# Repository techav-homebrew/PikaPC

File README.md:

# PikaPC

A PowerPC 403GA Homebrew Computer

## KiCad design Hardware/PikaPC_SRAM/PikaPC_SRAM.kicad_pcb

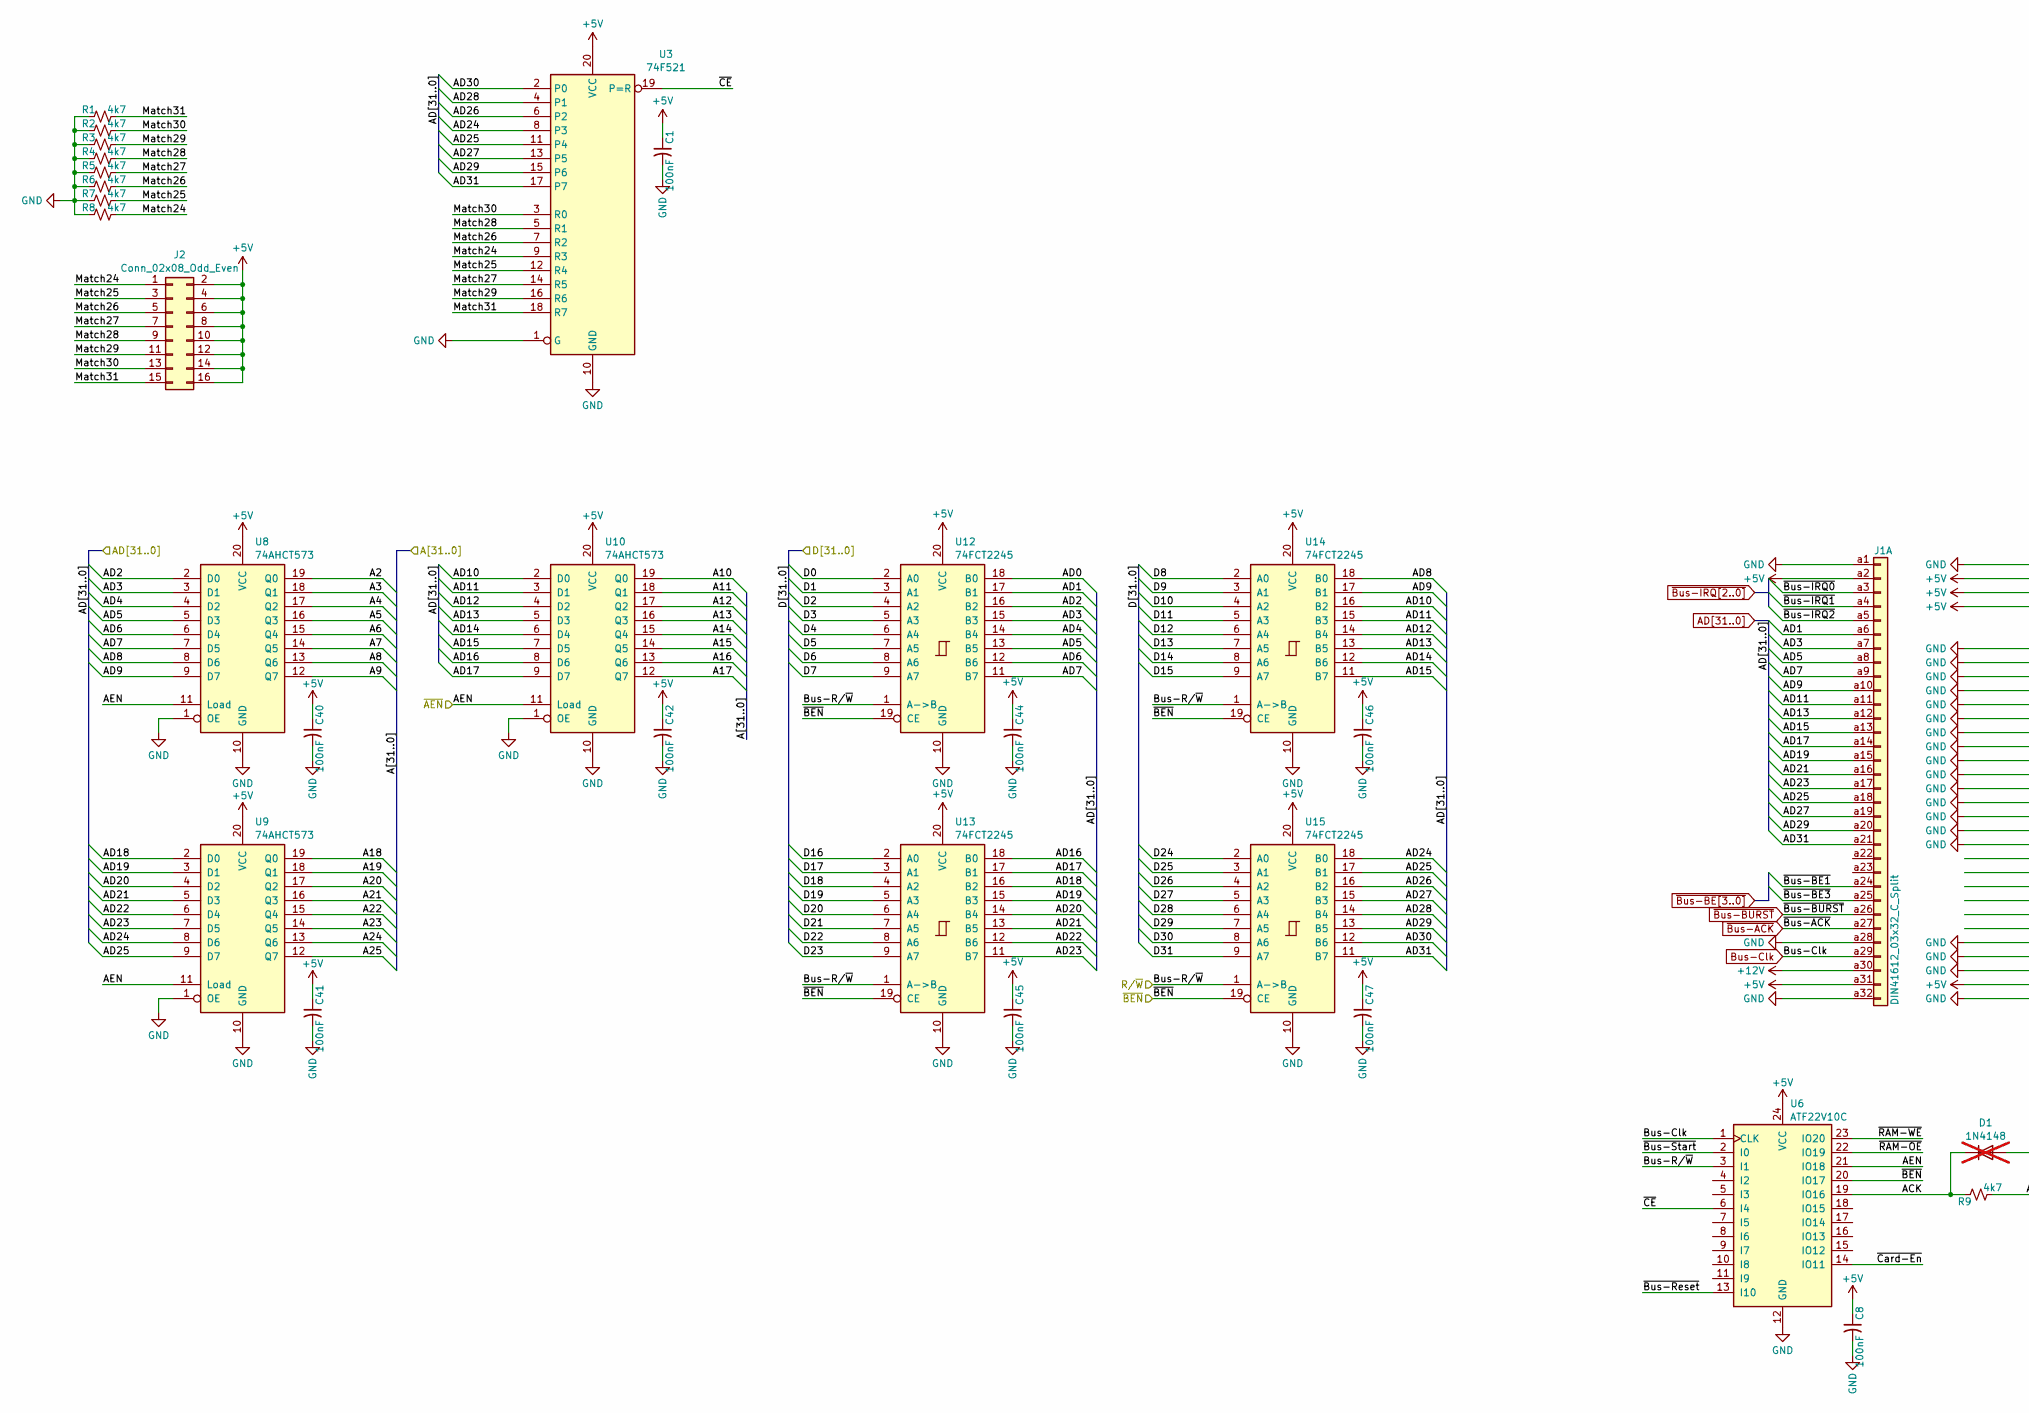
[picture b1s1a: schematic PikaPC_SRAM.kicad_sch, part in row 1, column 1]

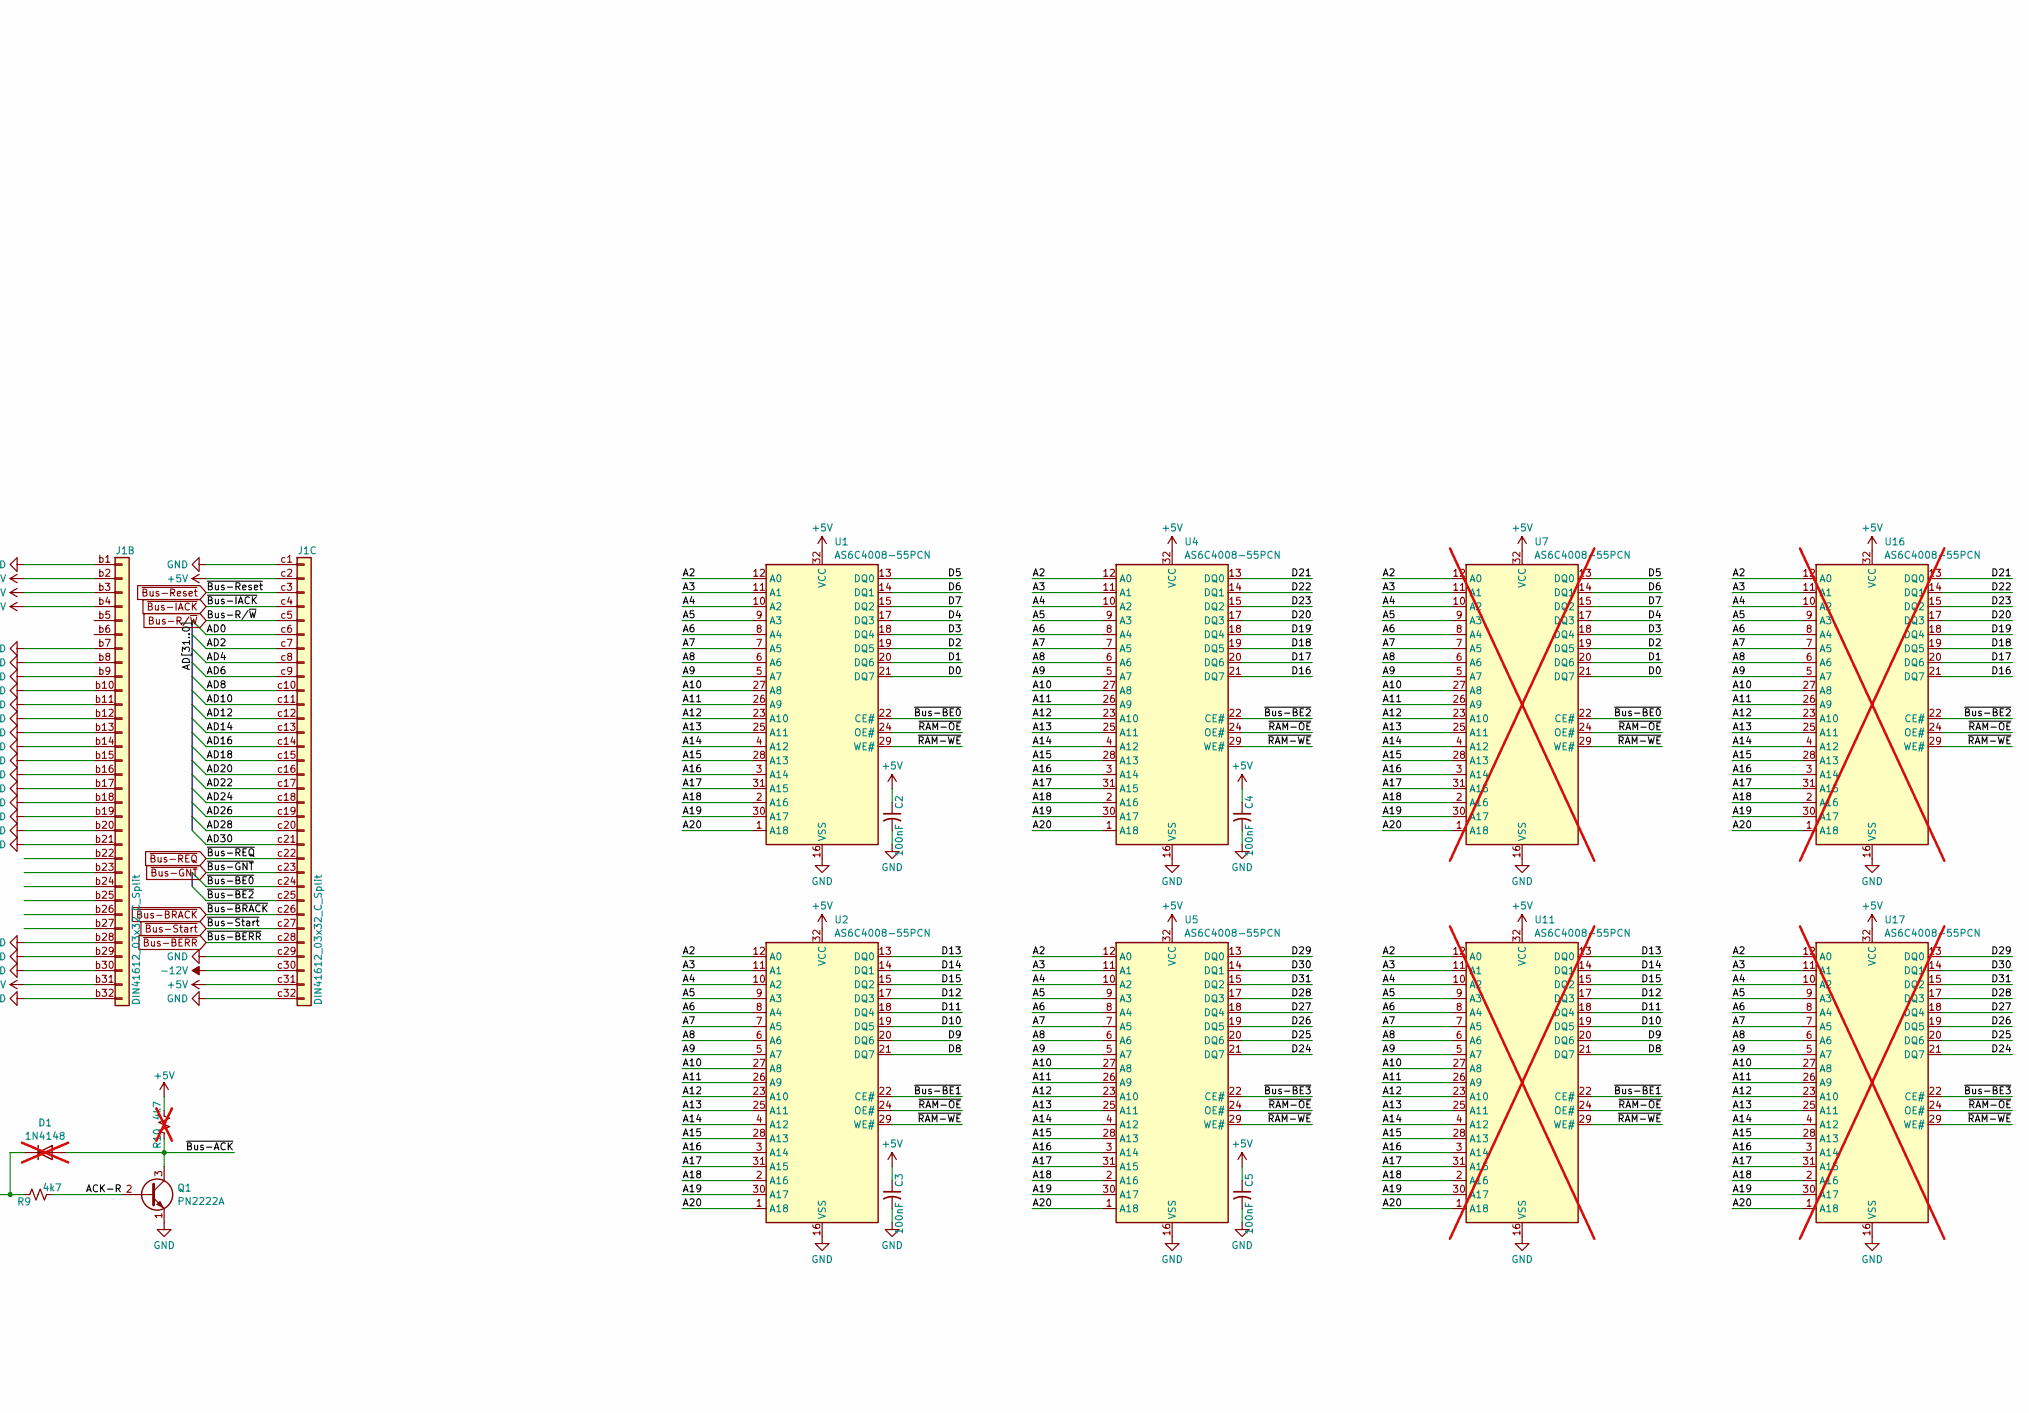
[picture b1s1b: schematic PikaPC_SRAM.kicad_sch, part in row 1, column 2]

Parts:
C1, C2, C3, C4, C5, C8, C40, C41, C42, C44, C45, C46, C47: 100nF; C_0805_2012Metric; Mouser 187-CL21B104KACNNNC
D1: 1N4148; D_DO-35_SOD27_P7.62mm_Horizontal; not fitted
J1: DIN41612_03x32_C_Split; DIN41612_C_3x32_Male_Horizontal_THT
J2: Conn_02x08_Odd_Even; PinHeader_2x08_P2.54mm_Vertical
Q1: PN2222A; TO-92_Inline
R1, R2, R3, R4, R5, R6, R7, R8, R9: 4k7; R_0805_2012Metric; Mouser 303-0805W8J0472T5E
R10: 4k7; R_0805_2012Metric; Mouser 303-0805W8J0472T5E; not fitted
U1, U2, U4, U5: AS6C4008-55PCN; DIP-32_W15.24mm
U3: 74F521; SOIC-20W_7.5x12.8mm_P1.27mm; Mouser 595-SN74F521DWR
U6: ATF22V10C; DIP-24_W7.62mm_Socket; Mouser 556-ATF22V10C-10PU
U7, U11, U16, U17: AS6C4008-55PCN; SOP-32_11.305x20.495mm_P1.27mm; not fitted
U8, U9, U10: 74AHCT573; TSSOP-20_4.4x6.5mm_P0.65mm; Mouser 771-74AHCT573PW-T
U12, U13, U14, U15: 74FCT2245; SOIC-20W_7.5x12.8mm_P1.27mm; Mouser 595-CY74FCT2245TSOCT

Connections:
+5V: C1.1, C2.1, C3.1, C4.1, C5.1, C8.1, C40.1, C41.1, C42.1, C44.1, C45.1, C46.1, C47.1, J1.a2, J1.a31, J1.b2, J1.b3, J1.b4, J1.b31, J1.c2, J1.c31, J2.2, J2.4, J2.6, J2.8, J2.10, J2.12, J2.14, J2.16, R10.2, U1.32 (VCC), U2.32 (VCC), U3.20 (VCC), U4.32 (VCC), U5.32 (VCC), U6.24 (VCC), U7.32 (VCC), U8.20 (VCC), U9.20 (VCC), U10.20 (VCC), U11.32 (VCC), U12.20 (VCC), U13.20 (VCC), U14.20 (VCC), U15.20 (VCC), U16.32 (VCC), U17.32 (VCC)
+12V: J1.a30
-12V: J1.c30
/A2: U1.12 (A0), U2.12 (A0), U4.12 (A0), U5.12 (A0), U7.12 (A0), U8.19 (Q0), U11.12 (A0), U16.12 (A0), U17.12 (A0)
/A3: U1.11 (A1), U2.11 (A1), U4.11 (A1), U5.11 (A1), U7.11 (A1), U8.18 (Q1), U11.11 (A1), U16.11 (A1), U17.11 (A1)
/A4: U1.10 (A2), U2.10 (A2), U4.10 (A2), U5.10 (A2), U7.10 (A2), U8.17 (Q2), U11.10 (A2), U16.10 (A2), U17.10 (A2)
/A5: U1.9 (A3), U2.9 (A3), U4.9 (A3), U5.9 (A3), U7.9 (A3), U8.16 (Q3), U11.9 (A3), U16.9 (A3), U17.9 (A3)
/A6: U1.8 (A4), U2.8 (A4), U4.8 (A4), U5.8 (A4), U7.8 (A4), U8.15 (Q4), U11.8 (A4), U16.8 (A4), U17.8 (A4)
/A7: U1.7 (A5), U2.7 (A5), U4.7 (A5), U5.7 (A5), U7.7 (A5), U8.14 (Q5), U11.7 (A5), U16.7 (A5), U17.7 (A5)
/A8: U1.6 (A6), U2.6 (A6), U4.6 (A6), U5.6 (A6), U7.6 (A6), U8.13 (Q6), U11.6 (A6), U16.6 (A6), U17.6 (A6)
/A9: U1.5 (A7), U2.5 (A7), U4.5 (A7), U5.5 (A7), U7.5 (A7), U8.12 (Q7), U11.5 (A7), U16.5 (A7), U17.5 (A7)
/A10: U1.27 (A8), U2.27 (A8), U4.27 (A8), U5.27 (A8), U7.27 (A8), U10.19 (Q0), U11.27 (A8), U16.27 (A8), U17.27 (A8)
/A11: U1.26 (A9), U2.26 (A9), U4.26 (A9), U5.26 (A9), U7.26 (A9), U10.18 (Q1), U11.26 (A9), U16.26 (A9), U17.26 (A9)
/A12: U1.23 (A10), U2.23 (A10), U4.23 (A10), U5.23 (A10), U7.23 (A10), U10.17 (Q2), U11.23 (A10), U16.23 (A10), U17.23 (A10)
/A13: U1.25 (A11), U2.25 (A11), U4.25 (A11), U5.25 (A11), U7.25 (A11), U10.16 (Q3), U11.25 (A11), U16.25 (A11), U17.25 (A11)
/A14: U1.4 (A12), U2.4 (A12), U4.4 (A12), U5.4 (A12), U7.4 (A12), U10.15 (Q4), U11.4 (A12), U16.4 (A12), U17.4 (A12)
/A15: U1.28 (A13), U2.28 (A13), U4.28 (A13), U5.28 (A13), U7.28 (A13), U10.14 (Q5), U11.28 (A13), U16.28 (A13), U17.28 (A13)
/A16: U1.3 (A14), U2.3 (A14), U4.3 (A14), U5.3 (A14), U7.3 (A14), U10.13 (Q6), U11.3 (A14), U16.3 (A14), U17.3 (A14)
/A17: U1.31 (A15), U2.31 (A15), U4.31 (A15), U5.31 (A15), U7.31 (A15), U10.12 (Q7), U11.31 (A15), U16.31 (A15), U17.31 (A15)
/A18: U1.2 (A16), U2.2 (A16), U4.2 (A16), U5.2 (A16), U7.2 (A16), U9.19 (Q0), U11.2 (A16), U16.2 (A16), U17.2 (A16)
/A19: U1.30 (A17), U2.30 (A17), U4.30 (A17), U5.30 (A17), U7.30 (A17), U9.18 (Q1), U11.30 (A17), U16.30 (A17), U17.30 (A17)
/A20: U1.1 (A18), U2.1 (A18), U4.1 (A18), U5.1 (A18), U7.1 (A18), U9.17 (Q2), U11.1 (A18), U16.1 (A18), U17.1 (A18)
/A21: U9.16 (Q3)
/A22: U9.15 (Q4)
/A23: U9.14 (Q5)
/A24: U9.13 (Q6)
/A25: U9.12 (Q7)
/ACK: D1.1 (K), R9.1, U6.19 (IO16)
/ACK-R: Q1.2 (B), R9.2
/AEN: U6.21 (IO18), U8.11 (Load), U9.11 (Load), U10.11 (Load)
/D0: U1.21 (DQ7), U7.21 (DQ7), U12.2 (A0)
/D1: U1.20 (DQ6), U7.20 (DQ6), U12.3 (A1)
/D2: U1.19 (DQ5), U7.19 (DQ5), U12.4 (A2)
/D3: U1.18 (DQ4), U7.18 (DQ4), U12.5 (A3)
/D4: U1.17 (DQ3), U7.17 (DQ3), U12.6 (A4)
/D5: U1.13 (DQ0), U7.13 (DQ0), U12.7 (A5)
/D6: U1.14 (DQ1), U7.14 (DQ1), U12.8 (A6)
/D7: U1.15 (DQ2), U7.15 (DQ2), U12.9 (A7)
/D8: U2.21 (DQ7), U11.21 (DQ7), U14.2 (A0)
/D9: U2.20 (DQ6), U11.20 (DQ6), U14.3 (A1)
/D10: U2.19 (DQ5), U11.19 (DQ5), U14.4 (A2)
/D11: U2.18 (DQ4), U11.18 (DQ4), U14.5 (A3)
/D12: U2.17 (DQ3), U11.17 (DQ3), U14.6 (A4)
/D13: U2.13 (DQ0), U11.13 (DQ0), U14.7 (A5)
/D14: U2.14 (DQ1), U11.14 (DQ1), U14.8 (A6)
/D15: U2.15 (DQ2), U11.15 (DQ2), U14.9 (A7)
/D16: U4.21 (DQ7), U13.2 (A0), U16.21 (DQ7)
/D17: U4.20 (DQ6), U13.3 (A1), U16.20 (DQ6)
/D18: U4.19 (DQ5), U13.4 (A2), U16.19 (DQ5)
/D19: U4.18 (DQ4), U13.5 (A3), U16.18 (DQ4)
/D20: U4.17 (DQ3), U13.6 (A4), U16.17 (DQ3)
/D21: U4.13 (DQ0), U13.7 (A5), U16.13 (DQ0)
/D22: U4.14 (DQ1), U13.8 (A6), U16.14 (DQ1)
/D23: U4.15 (DQ2), U13.9 (A7), U16.15 (DQ2)
/D24: U5.21 (DQ7), U15.2 (A0), U17.21 (DQ7)
/D25: U5.20 (DQ6), U15.3 (A1), U17.20 (DQ6)
/D26: U5.19 (DQ5), U15.4 (A2), U17.19 (DQ5)
/D27: U5.18 (DQ4), U15.5 (A3), U17.18 (DQ4)
/D28: U5.17 (DQ3), U15.6 (A4), U17.17 (DQ3)
/D29: U5.13 (DQ0), U15.7 (A5), U17.13 (DQ0)
/D30: U5.14 (DQ1), U15.8 (A6), U17.14 (DQ1)
/D31: U5.15 (DQ2), U15.9 (A7), U17.15 (DQ2)
/Match24: J2.1, R8.2, U3.9 (R3)
/Match25: J2.3, R7.2, U3.12 (R4)
/Match26: J2.5, R6.2, U3.7 (R2)
/Match27: J2.7, R5.2, U3.14 (R5)
/Match28: J2.9, R4.2, U3.5 (R1)
/Match29: J2.11, R3.2, U3.16 (R6)
/Match30: J2.13, R2.2, U3.3 (R0)
/Match31: J2.15, R1.2, U3.18 (R7)
/~BEN: U6.20 (IO17), U12.19 (CE), U13.19 (CE), U14.19 (CE), U15.19 (CE)
/~CE: U3.19 (P=R), U6.6 (I4)
/~Card-En: U6.14 (IO11)
/~RAM-OE: U1.24 (OE#), U2.24 (OE#), U4.24 (OE#), U5.24 (OE#), U6.22 (IO19), U7.24 (OE#), U11.24 (OE#), U16.24 (OE#), U17.24 (OE#)
/~RAM-WE: U1.29 (WE#), U2.29 (WE#), U4.29 (WE#), U5.29 (WE#), U6.23 (IO20), U7.29 (WE#), U11.29 (WE#), U16.29 (WE#), U17.29 (WE#)
AD0: J1.c6, U12.18 (B0)
AD1: J1.a6, U12.17 (B1)
AD2: J1.c7, U8.2 (D0), U12.16 (B2)
AD3: J1.a7, U8.3 (D1), U12.15 (B3)
AD4: J1.c8, U8.4 (D2), U12.14 (B4)
AD5: J1.a8, U8.5 (D3), U12.13 (B5)
AD6: J1.c9, U8.6 (D4), U12.12 (B6)
AD7: J1.a9, U8.7 (D5), U12.11 (B7)
AD8: J1.c10, U8.8 (D6), U14.18 (B0)
AD9: J1.a10, U8.9 (D7), U14.17 (B1)
AD10: J1.c11, U10.2 (D0), U14.16 (B2)
AD11: J1.a11, U10.3 (D1), U14.15 (B3)
AD12: J1.c12, U10.4 (D2), U14.14 (B4)
AD13: J1.a12, U10.5 (D3), U14.13 (B5)
AD14: J1.c13, U10.6 (D4), U14.12 (B6)
AD15: J1.a13, U10.7 (D5), U14.11 (B7)
AD16: J1.c14, U10.8 (D6), U13.18 (B0)
AD17: J1.a14, U10.9 (D7), U13.17 (B1)
AD18: J1.c15, U9.2 (D0), U13.16 (B2)
AD19: J1.a15, U9.3 (D1), U13.15 (B3)
AD20: J1.c16, U9.4 (D2), U13.14 (B4)
AD21: J1.a16, U9.5 (D3), U13.13 (B5)
AD22: J1.c17, U9.6 (D4), U13.12 (B6)
AD23: J1.a17, U9.7 (D5), U13.11 (B7)
AD24: J1.c18, U3.8 (P3), U9.8 (D6), U15.18 (B0)
AD25: J1.a18, U3.11 (P4), U9.9 (D7), U15.17 (B1)
AD26: J1.c19, U3.6 (P2), U15.16 (B2)
AD27: J1.a19, U3.13 (P5), U15.15 (B3)
AD28: J1.c20, U3.4 (P1), U15.14 (B4)
AD29: J1.a20, U3.15 (P6), U15.13 (B5)
AD30: J1.c21, U3.2 (P0), U15.12 (B6)
AD31: J1.a21, U3.17 (P7), U15.11 (B7)
Bus-Clk: J1.a29, U6.1 (CLK)
Bus-R/~W: J1.c5, U6.3 (I1), U12.1 (A->B), U13.1 (A->B), U14.1 (A->B), U15.1 (A->B)
GND: C1.2, C2.2, C3.2, C4.2, C5.2, C8.2, C40.2, C41.2, C42.2, C44.2, C45.2, C46.2, C47.2, J1.a1, J1.a28, J1.a32, J1.b1, J1.b7, J1.b8, J1.b9, J1.b10, J1.b11, J1.b12, J1.b13, J1.b14, J1.b15, J1.b16, J1.b17, J1.b18, J1.b19, J1.b20, J1.b21, J1.b28, J1.b29, J1.b30, J1.b32, J1.c1, J1.c29, J1.c32, Q1.1 (E), R1.1, R2.1, R3.1, R4.1, R5.1, R6.1, R7.1, R8.1, U1.16 (VSS), U2.16 (VSS), U3.1 (G), U3.10 (GND), U4.16 (VSS), U5.16 (VSS), U6.12 (GND), U7.16 (VSS), U8.1 (OE), U8.10 (GND), U9.1 (OE), U9.10 (GND), U10.1 (OE), U10.10 (GND), U11.16 (VSS), U12.10 (GND), U13.10 (GND), U14.10 (GND), U15.10 (GND), U16.16 (VSS), U17.16 (VSS)
~Bus-ACK: D1.2 (A), J1.a27, Q1.3 (C), R10.1
~Bus-BE0: J1.c24, U1.22 (CE#), U7.22 (CE#)
~Bus-BE1: J1.a24, U2.22 (CE#), U11.22 (CE#)
~Bus-BE2: J1.c25, U4.22 (CE#), U16.22 (CE#)
~Bus-BE3: J1.a25, U5.22 (CE#), U17.22 (CE#)
~Bus-BERR: J1.c28
~Bus-BRACK: J1.c26
~Bus-BURST: J1.a26
~Bus-GNT: J1.c23
~Bus-IACK: J1.c4
~Bus-IRQ0: J1.a3
~Bus-IRQ1: J1.a4
~Bus-IRQ2: J1.a5
~Bus-REQ: J1.c22
~Bus-Reset: J1.c3, U6.13 (I10)
~Bus-Start: J1.c27, U6.2 (I0)

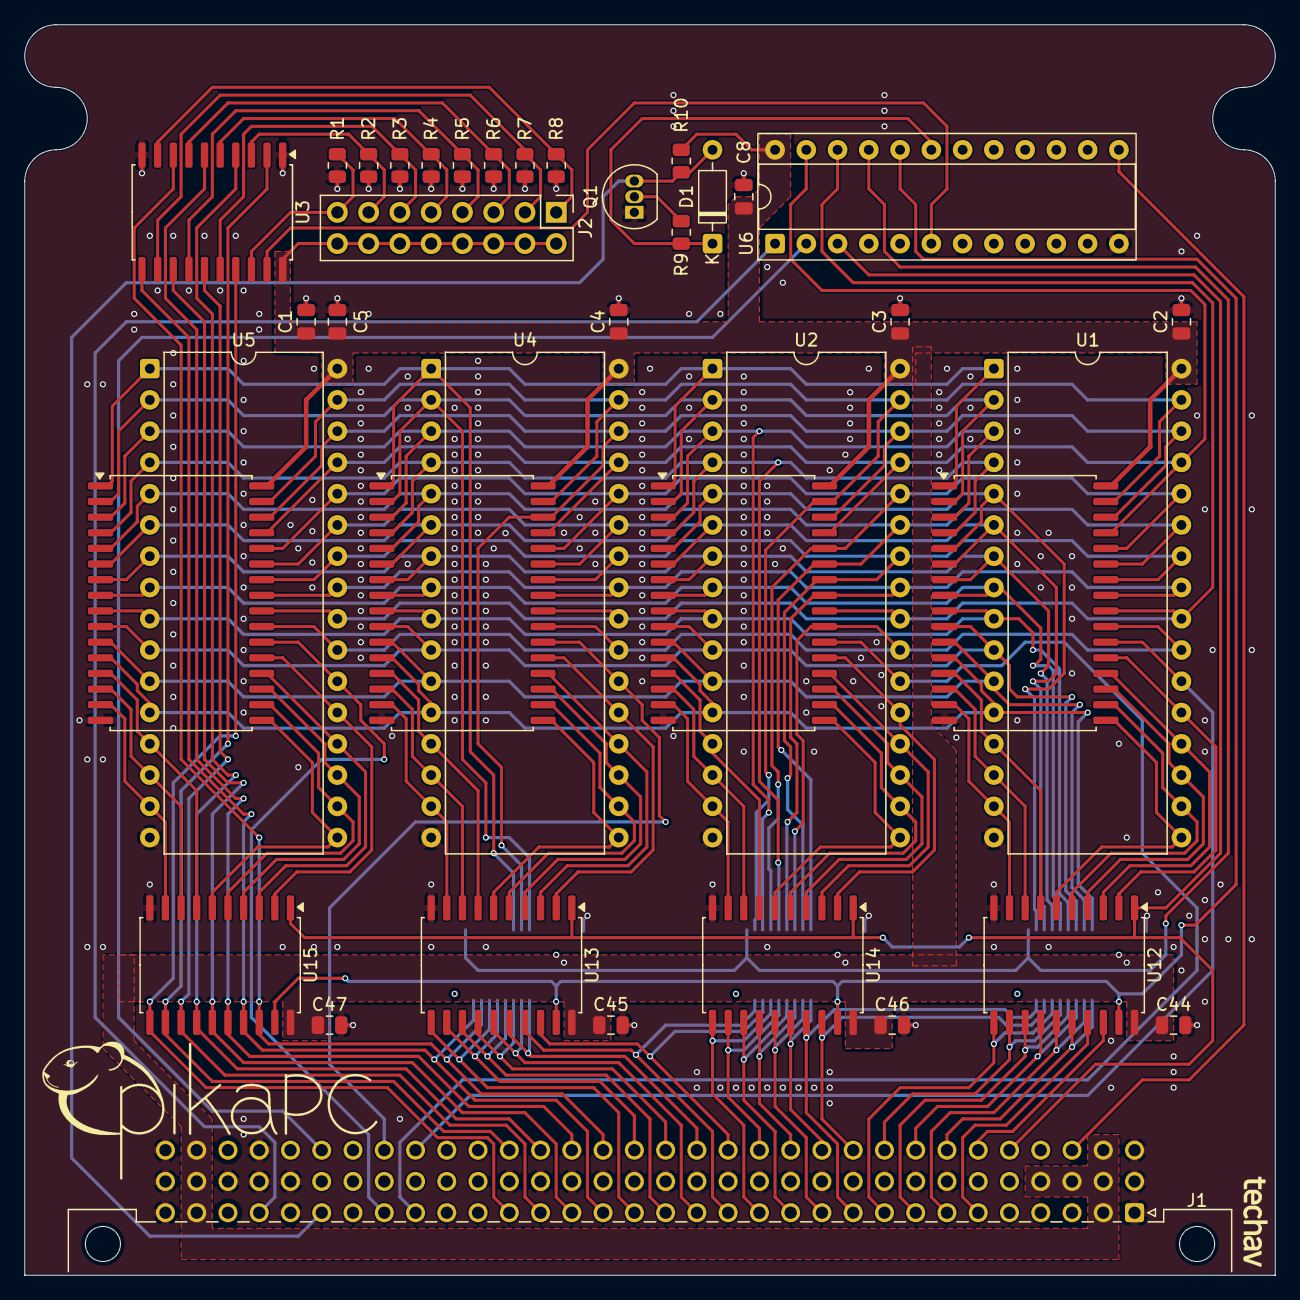
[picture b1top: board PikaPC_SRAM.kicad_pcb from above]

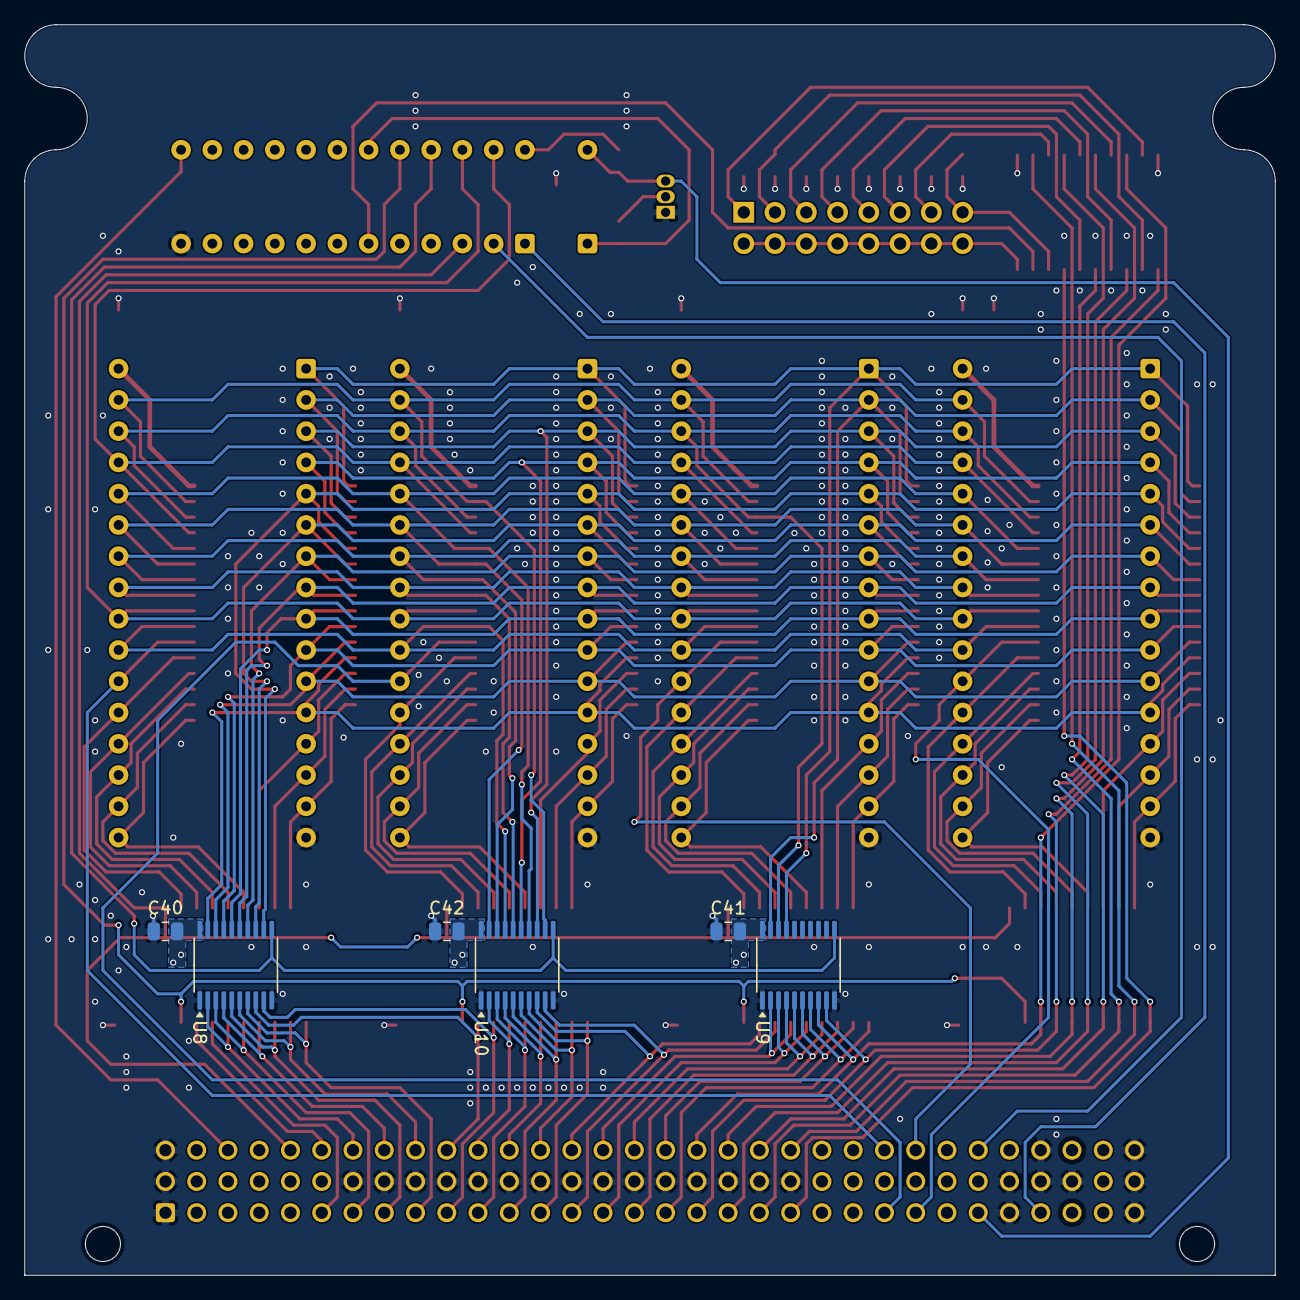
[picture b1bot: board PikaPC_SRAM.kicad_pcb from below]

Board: 2 copper layers, 101.6 x 101.6 mm, 44 parts (6 on the bottom side), 109 nets.

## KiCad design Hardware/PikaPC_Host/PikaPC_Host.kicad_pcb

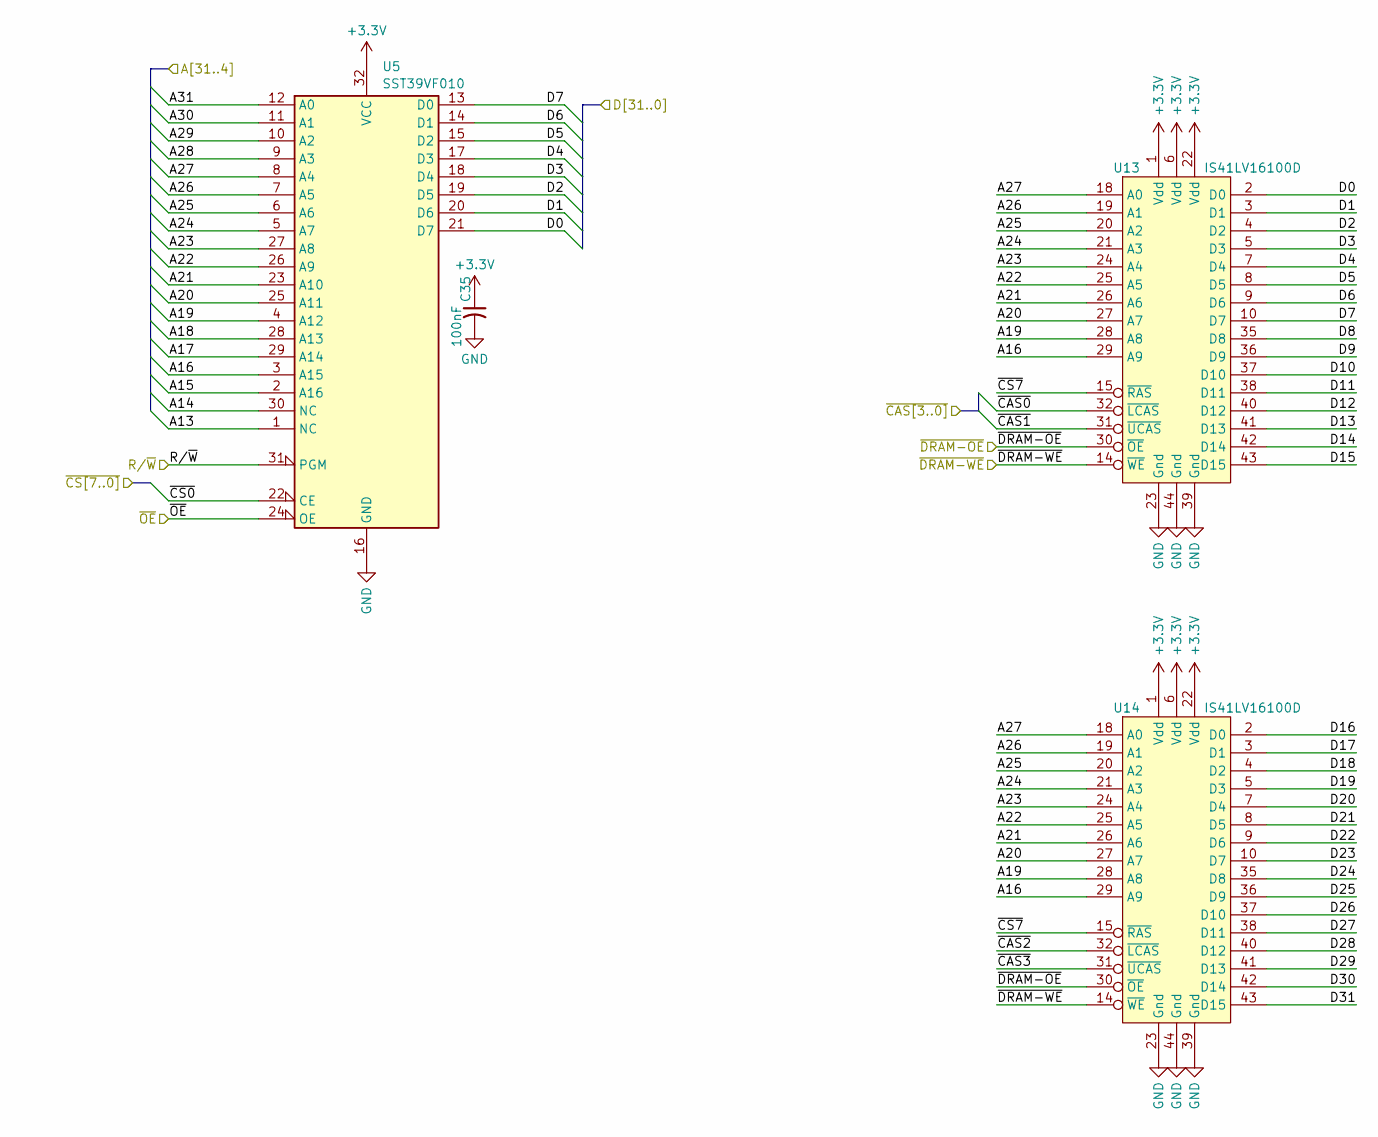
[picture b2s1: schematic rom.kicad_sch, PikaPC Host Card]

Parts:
C35: 100nF; C_0805_2012Metric; Mouser 187-CL21B104KACNNNC
U5: SST39VF010; PLCC-32_THT-Socket; Mouser 804-39VF0107INHE-T
U13, U14: IS41LV16100D; TSOP-II-44

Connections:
+3.3V: C35.1, U5.32 (VCC), U13.1 (Vdd), U13.6 (Vdd), U13.22 (Vdd), U14.1 (Vdd), U14.6 (Vdd), U14.22 (Vdd); also elsewhere on the board
/CPU Bus/D0: U5.21 (D7), U13.2 (D0); also elsewhere on the board
/CPU Bus/D1: U5.20 (D6), U13.3 (D1); also elsewhere on the board
/CPU Bus/D2: U5.19 (D5), U13.4 (D2); also elsewhere on the board
/CPU Bus/D3: U5.18 (D4), U13.5 (D3); also elsewhere on the board
/CPU Bus/D4: U5.17 (D3), U13.7 (D4); also elsewhere on the board
/CPU Bus/D5: U5.15 (D2), U13.8 (D5); also elsewhere on the board
/CPU Bus/D6: U5.14 (D1), U13.9 (D6); also elsewhere on the board
/CPU Bus/D7: U5.13 (D0), U13.10 (D7); also elsewhere on the board
/CPU Bus/D8: U13.35 (D8); also elsewhere on the board
/CPU Bus/D9: U13.36 (D9); also elsewhere on the board
/CPU Bus/D10: U13.37 (D10); also elsewhere on the board
/CPU Bus/D11: U13.38 (D11); also elsewhere on the board
/CPU Bus/D12: U13.40 (D12); also elsewhere on the board
/CPU Bus/D13: U13.41 (D13); also elsewhere on the board
/CPU Bus/D14: U13.42 (D14); also elsewhere on the board
/CPU Bus/D15: U13.43 (D15); also elsewhere on the board
/CPU Bus/D16: U14.2 (D0); also elsewhere on the board
/CPU Bus/D17: U14.3 (D1); also elsewhere on the board
/CPU Bus/D18: U14.4 (D2); also elsewhere on the board
/CPU Bus/D19: U14.5 (D3); also elsewhere on the board
/CPU Bus/D20: U14.7 (D4); also elsewhere on the board
/CPU Bus/D21: U14.8 (D5); also elsewhere on the board
/CPU Bus/D22: U14.9 (D6); also elsewhere on the board
/CPU Bus/D23: U14.10 (D7); also elsewhere on the board
/CPU Bus/D24: U14.35 (D8); also elsewhere on the board
/CPU Bus/D25: U14.36 (D9); also elsewhere on the board
/CPU Bus/D26: U14.37 (D10); also elsewhere on the board
/CPU Bus/D27: U14.38 (D11); also elsewhere on the board
/CPU Bus/D28: U14.40 (D12); also elsewhere on the board
/CPU Bus/D29: U14.41 (D13); also elsewhere on the board
/CPU Bus/D30: U14.42 (D14); also elsewhere on the board
/CPU Bus/D31: U14.43 (D15); also elsewhere on the board
/CPU Bus/~CAS0: U13.32 (~LCAS); also elsewhere on the board
/CPU Bus/~CAS1: U13.31 (~UCAS); also elsewhere on the board
/CPU Bus/~CAS2: U14.32 (~LCAS); also elsewhere on the board
/CPU Bus/~CAS3: U14.31 (~UCAS); also elsewhere on the board
/CPU Bus/~CS0: U5.22 (CE); also elsewhere on the board
/CPU Bus/~CS7: U13.15 (~RAS), U14.15 (~RAS); also elsewhere on the board
/CPU Bus/~DRAM-OE: U13.30 (~OE), U14.30 (~OE); also elsewhere on the board
/CPU Bus/~DRAM-WE: U13.14 (~WE), U14.14 (~WE); also elsewhere on the board
/CPU Bus/~OE: U5.24 (OE); also elsewhere on the board
/Main Bus/A13: U5.1 (NC); also elsewhere on the board
/Main Bus/A14: U5.30 (NC); also elsewhere on the board
/Main Bus/A15: U5.2 (A16); also elsewhere on the board
/Main Bus/A16: U5.3 (A15), U13.29 (A9), U14.29 (A9); also elsewhere on the board
/Main Bus/A17: U5.29 (A14); also elsewhere on the board
/Main Bus/A18: U5.28 (A13); also elsewhere on the board
/Main Bus/A19: U5.4 (A12), U13.28 (A8), U14.28 (A8); also elsewhere on the board
/Main Bus/A20: U5.25 (A11), U13.27 (A7), U14.27 (A7); also elsewhere on the board
/Main Bus/A21: U5.23 (A10), U13.26 (A6), U14.26 (A6); also elsewhere on the board
/Main Bus/A22: U5.26 (A9), U13.25 (A5), U14.25 (A5); also elsewhere on the board
/Main Bus/A23: U5.27 (A8), U13.24 (A4), U14.24 (A4); also elsewhere on the board
/Main Bus/A24: U5.5 (A7), U13.21 (A3), U14.21 (A3); also elsewhere on the board
/Main Bus/A25: U5.6 (A6), U13.20 (A2), U14.20 (A2); also elsewhere on the board
/Main Bus/A26: U5.7 (A5), U13.19 (A1), U14.19 (A1); also elsewhere on the board
/Main Bus/A27: U5.8 (A4), U13.18 (A0), U14.18 (A0); also elsewhere on the board
/Main Bus/A28: U5.9 (A3); also elsewhere on the board
/Main Bus/A29: U5.10 (A2); also elsewhere on the board
/Main Bus/A30: U5.11 (A1); also elsewhere on the board
/Main Bus/A31: U5.12 (A0); also elsewhere on the board
/R/~W: U5.31 (PGM); also elsewhere on the board
